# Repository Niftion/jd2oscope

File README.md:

## Project Status

- `3dmodels/`: Iteration 1 complete; iteration 2 WIP
  - Considering different potentiometer & button models (pot.s too small for knobs)
  - Looking into overhead enclosure for button/knob interface (i.e., transitioning from partially exposed to fully enclosed)
- `firmware/`: Iteration 1 WIP
  - Currently troubleshooting issues with SPI comm.; assumed resolution w/ the inclusion of tri-state buffer
  - Potentiometers laggy; assumed resolution w/ swap for rotary encoders
- `hardware/`: Iteration 1 complete; iteration 2 WIP
  - Adjustments needed to account for pullups/pulldowns & tri-state buffer
  - Considering swapping potentiometers for rotary encoders & using different buttons
  - Potentially re-evaluate netclasses/copper trace thicknesses
  - Flip around opAmp (for some reason was inverted in schematics)
  - Ensure all passives' values *actually exist* (if not, modify circuit to use ones that do)
  - Swap 5V LDO to buck converter (& generally re-evaluate power distribution method (currently not adequate for long-term usage))

## Project Leads

- `3dmodels/`: [@kaylauyema](https://github.com/kaylauyema)
  - *See [Onshape](https://cad.onshape.com/documents/8ccdb21e8d1079c729b3d0f6/w/fb9eb84c8df37a115b39a8e3/e/654db45d68c6c467c0a4227c?renderMode=0&uiState=67cde4469e5450083d885918) for all CAD files*
- `firmware/`: [@StPelican42](https://github.com/StPelican42)
- `hardware/`: [@Niftion](https://github.com/Niftion)

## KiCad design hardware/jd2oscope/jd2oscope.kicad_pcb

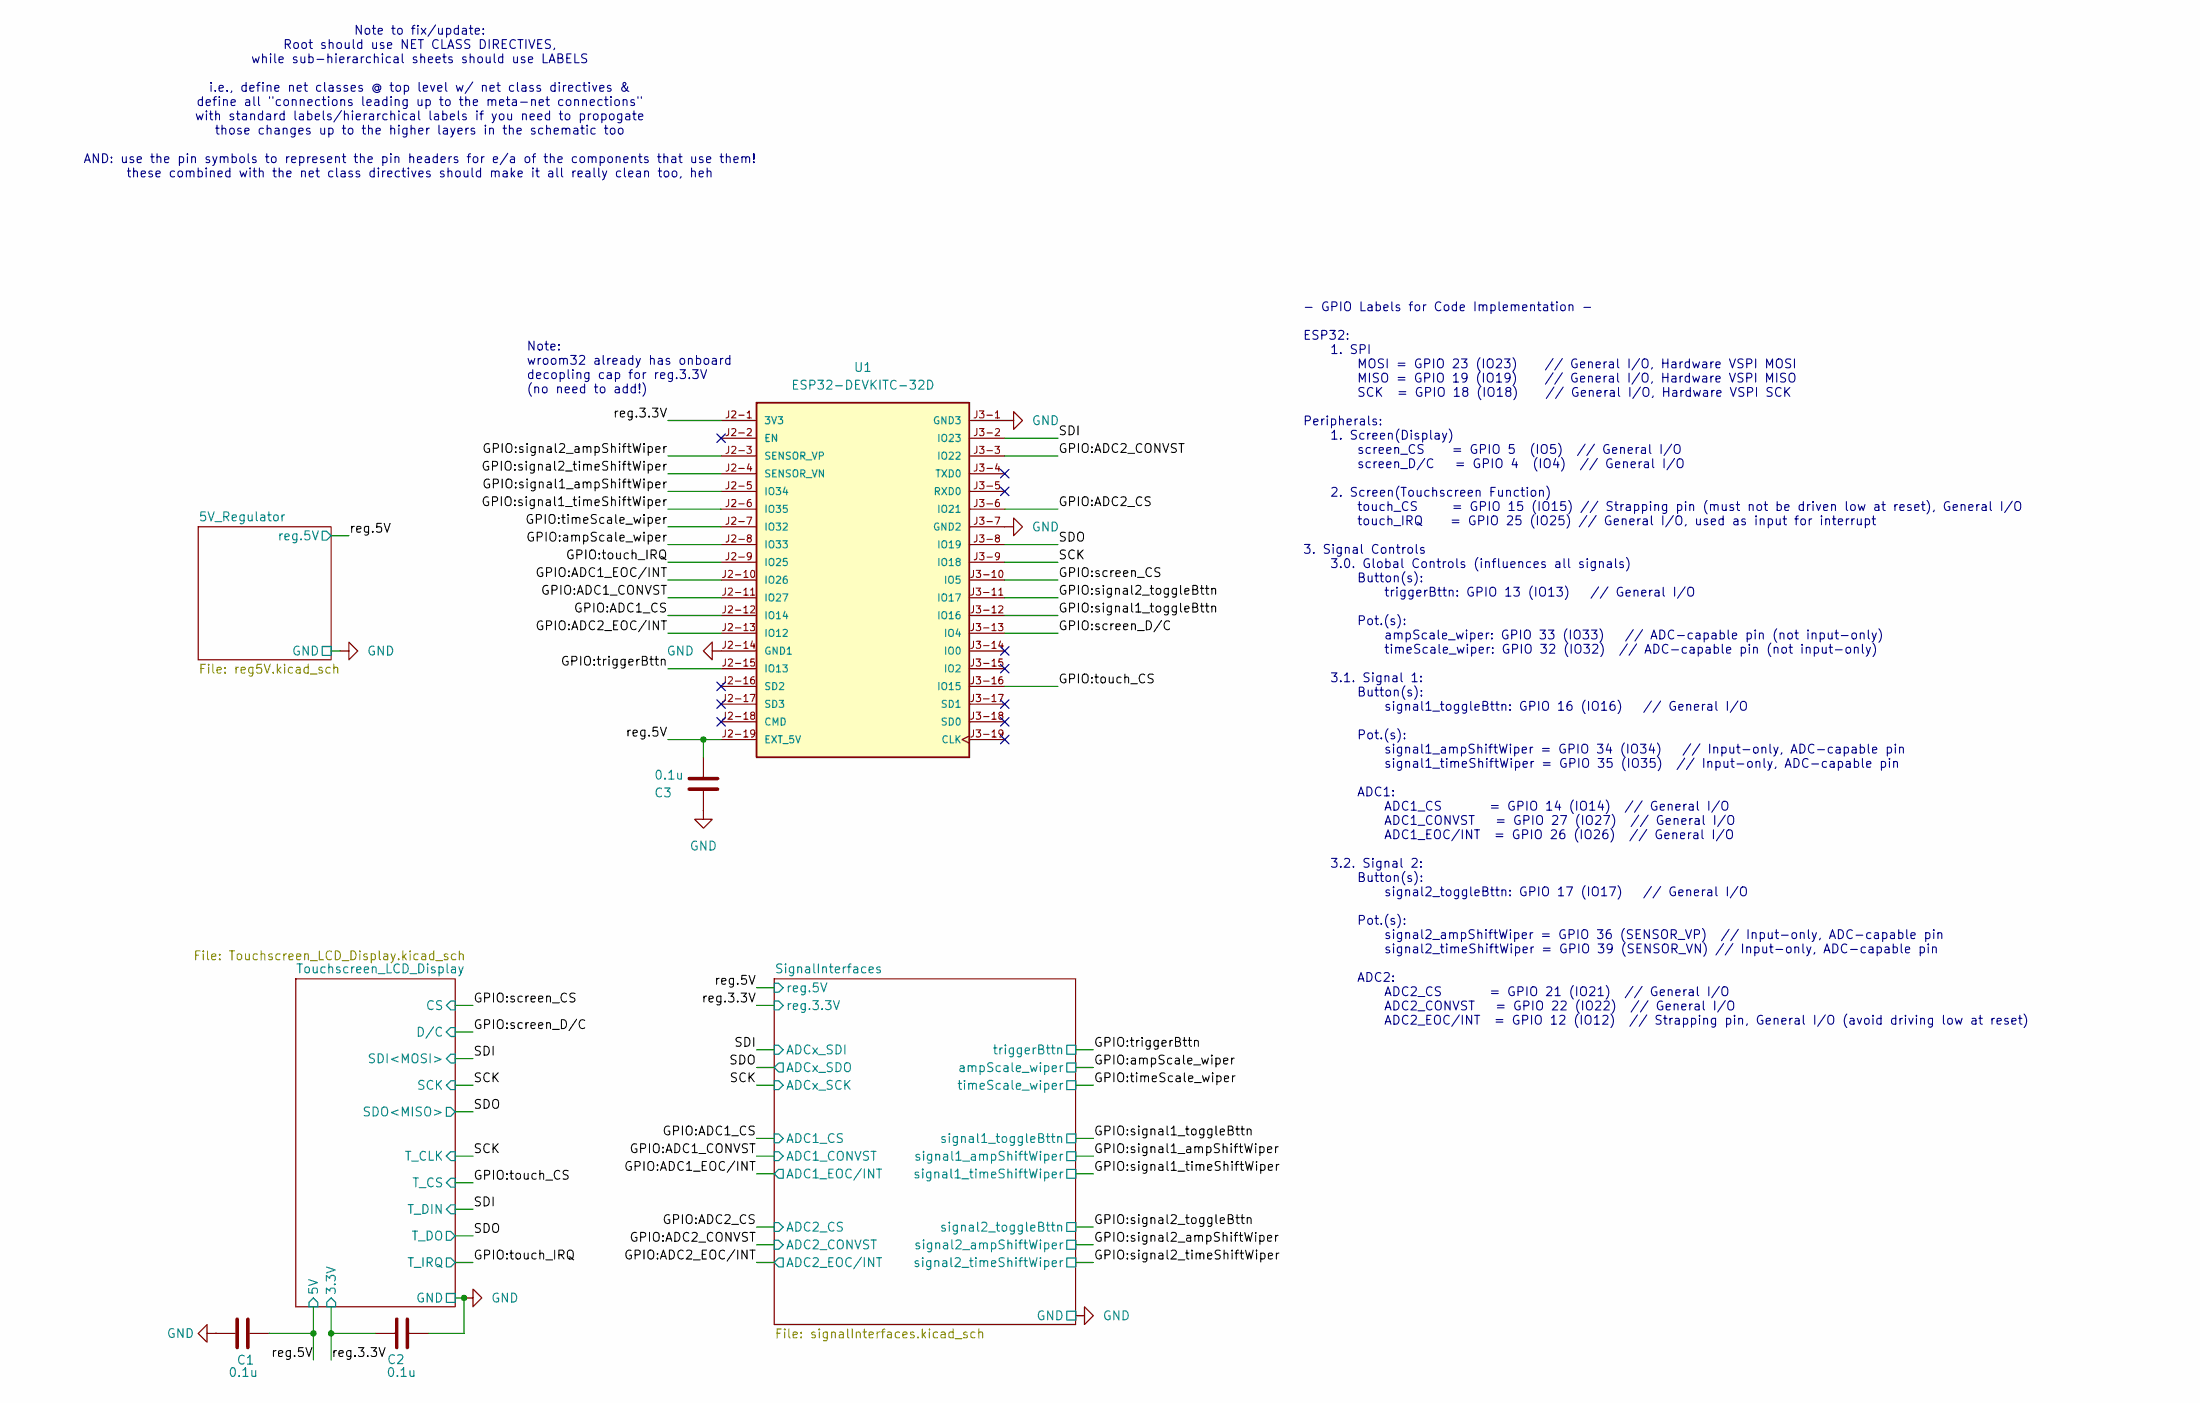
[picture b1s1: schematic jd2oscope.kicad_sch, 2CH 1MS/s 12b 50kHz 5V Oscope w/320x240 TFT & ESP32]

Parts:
C1, C2, C3: 0.1u; C_0603_1608Metric_Pad1.08x0.95mm_HandSolder
U1: ESP32-DEVKITC-32D; MODULE_ESP32-DEVKITC-32D; PARTREV V4; DigiKey_Part_Number 4166-ESP32-DEVKITC-32D-ND

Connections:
/GPIO:ADC1_CONVST: U1.J2-11 (IO27); also elsewhere on the board
/GPIO:ADC1_CS: U1.J2-12 (IO14); also elsewhere on the board
/GPIO:ADC1_EOC/INT: U1.J2-10 (IO26); also elsewhere on the board
/GPIO:ADC2_CONVST: U1.J3-3 (IO22); also elsewhere on the board
/GPIO:ADC2_CS: U1.J3-6 (IO21); also elsewhere on the board
/GPIO:ADC2_EOC/INT: U1.J2-13 (IO12); also elsewhere on the board
/GPIO:ampScale_wiper: U1.J2-8 (IO33); also elsewhere on the board
/GPIO:screen_CS: U1.J3-10 (IO5); also elsewhere on the board
/GPIO:screen_D/C: U1.J3-13 (IO4); also elsewhere on the board
/GPIO:signal1_ampShiftWiper: U1.J2-5 (IO34); also elsewhere on the board
/GPIO:signal1_timeShiftWiper: U1.J2-6 (IO35); also elsewhere on the board
/GPIO:signal1_toggleBttn: U1.J3-12 (IO16); also elsewhere on the board
/GPIO:signal2_ampShiftWiper: U1.J2-3 (SENSOR_VP); also elsewhere on the board
/GPIO:signal2_timeShiftWiper: U1.J2-4 (SENSOR_VN); also elsewhere on the board
/GPIO:signal2_toggleBttn: U1.J3-11 (IO17); also elsewhere on the board
/GPIO:timeScale_wiper: U1.J2-7 (IO32); also elsewhere on the board
/GPIO:touch_CS: U1.J3-16 (IO15); also elsewhere on the board
/GPIO:touch_IRQ: U1.J2-9 (IO25); also elsewhere on the board
/GPIO:triggerBttn: U1.J2-15 (IO13); also elsewhere on the board
/SCK: U1.J3-9 (IO18); also elsewhere on the board
/SDI: U1.J3-2 (IO23); also elsewhere on the board
/SDO: U1.J3-8 (IO19); also elsewhere on the board
/reg.3.3V: C2.2, U1.J2-1 (3V3); also elsewhere on the board
/reg.5V: C1.2, C3.2, U1.J2-19 (EXT_5V); also elsewhere on the board
GND: C1.1, C2.1, C3.1, U1.J2-14 (GND1), U1.J3-1 (GND3), U1.J3-7 (GND2); also elsewhere on the board

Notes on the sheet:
Note to fix/update: Root should use NET CLASS DIRECTIVES, while sub-hierarchical sheets should use LABELS i.e., define net classes @ top level w/ net class directives & define all "connections leading up to the meta-net connections" with standard labels/hierarchical labels if you need to propogate 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
- GPIO Labels for Code Implementation - ESP32: 1. SPI MOSI = GPIO 23 (IO23) // General I/O, Hardware VSPI MOSI MISO = GPIO 19 (IO19) // General I/O, Hardware VSPI MISO SCK = GPIO 18 (IO18) // General I/O, Hardware VSPI SCK Peripherals: 1. Screen(Display) screen_CS = GPIO 5 (IO5) // General I/O scre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
Note: wroom32 already has onboard decopling cap for reg.3.3V (no need to add!)

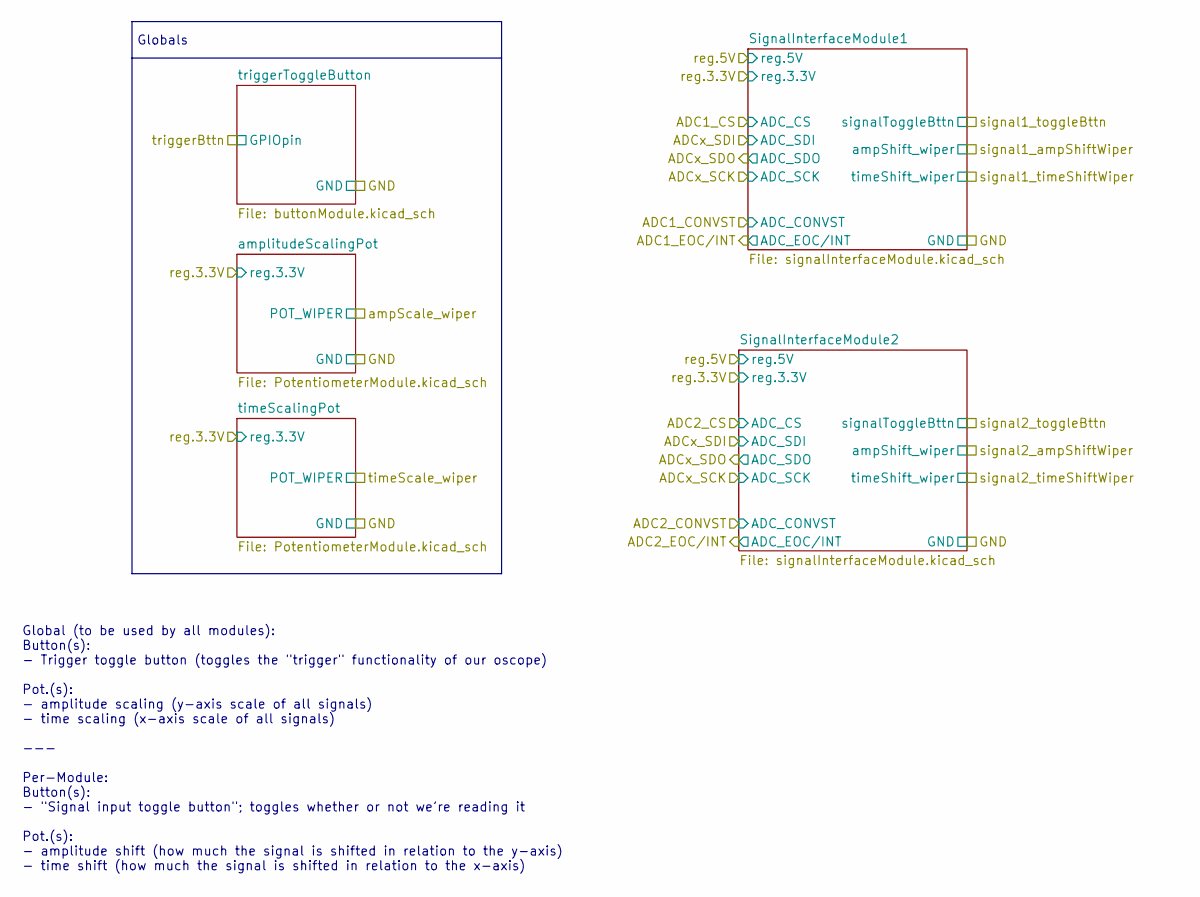
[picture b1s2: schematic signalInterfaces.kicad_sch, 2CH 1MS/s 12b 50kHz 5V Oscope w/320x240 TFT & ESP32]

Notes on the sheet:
Globals
Global (to be used by all modules): Button(s): - Trigger toggle button (toggles the "trigger" functionality of our oscope) Pot.(s): - amplitude scaling (y-axis scale of all signals) - time scaling (x-axis scale of all signals) --- Per-Module: Button(s): - "Signal input toggle button"; toggles wheth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

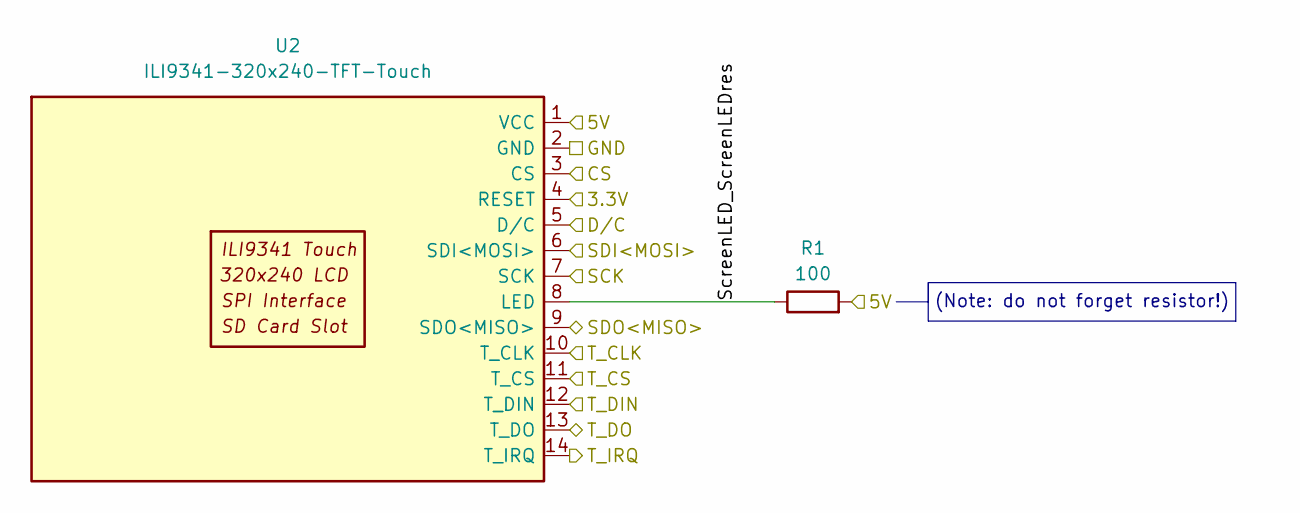
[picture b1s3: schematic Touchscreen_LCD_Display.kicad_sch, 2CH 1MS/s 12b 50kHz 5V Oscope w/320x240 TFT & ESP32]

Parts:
R1: 100; R_0603_1608Metric_Pad0.98x0.95mm_HandSolder
U2: ILI9341-320x240-TFT-Touch; PinHeader_1x14_P2.54mm_Vertical

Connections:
/GPIO:screen_CS: U2.3 (CS); also elsewhere on the board
/GPIO:screen_D/C: U2.5 (D/C); also elsewhere on the board
/GPIO:touch_CS: U2.11 (T_CS); also elsewhere on the board
/GPIO:touch_IRQ: U2.14 (T_IRQ); also elsewhere on the board
/SCK: U2.7 (SCK), U2.10 (T_CLK); also elsewhere on the board
/SDI: U2.6 (SDI<MOSI>), U2.12 (T_DIN); also elsewhere on the board
/SDO: U2.9 (SDO<MISO>), U2.13 (T_DO); also elsewhere on the board
/Touchscreen_LCD_Display/ScreenLED_ScreenLEDres: R1.1, U2.8 (LED)
/reg.3.3V: U2.4 (RESET); also elsewhere on the board
/reg.5V: R1.2, U2.1 (VCC); also elsewhere on the board
GND: U2.2 (GND); also elsewhere on the board

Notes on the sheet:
(Note: do not forget resistor!)

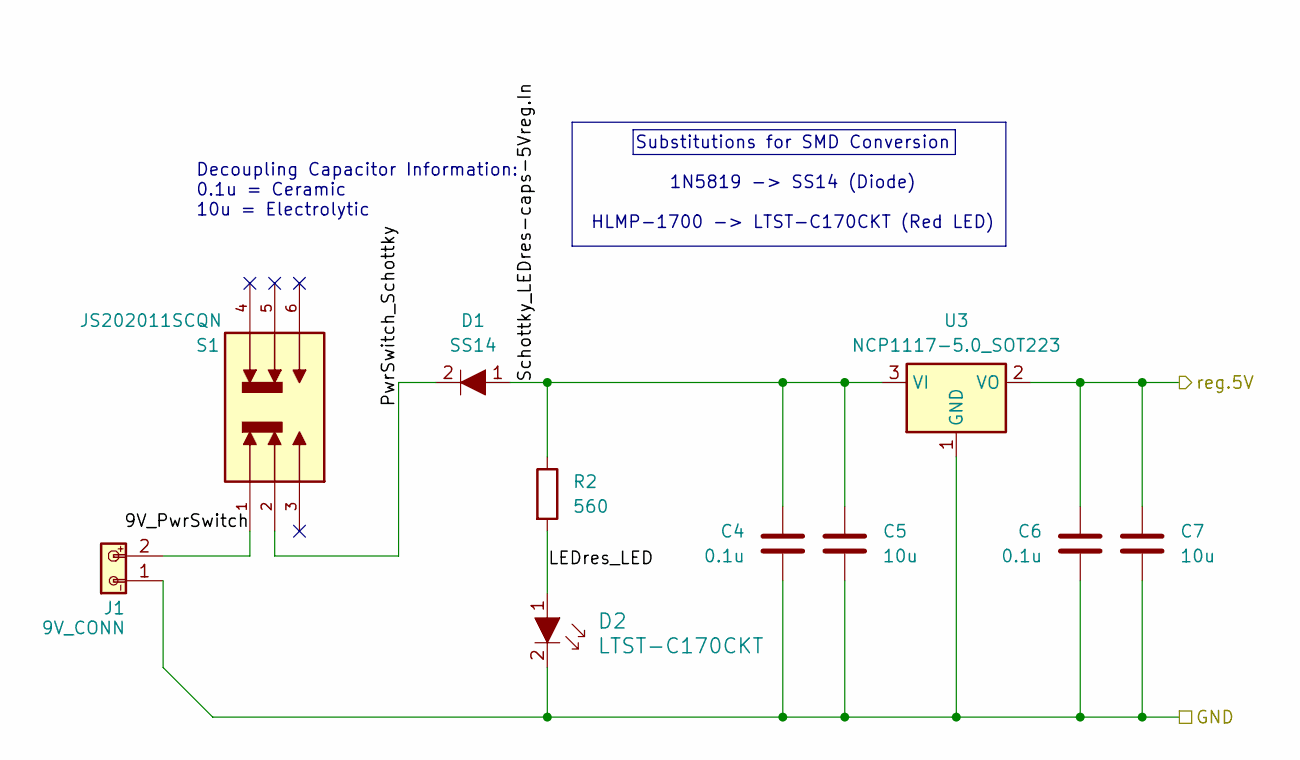
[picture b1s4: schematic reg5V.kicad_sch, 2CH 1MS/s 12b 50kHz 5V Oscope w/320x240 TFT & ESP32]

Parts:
C4, C6: 0.1u; C_0603_1608Metric_Pad1.08x0.95mm_HandSolder
C5, C7: 10u; C_0603_1608Metric_Pad1.08x0.95mm_HandSolder
D1: SS14; D_SOD-123; MPN SS14; Digi-Key_PN SS14CT-ND
D2: LTST-C170CKT; LED_0805_2012Metric; MPN LTST-C170KFKT; Digi-Key_PN 160-1184-1-ND
J1: 9V_CONN; TerminalBlock_RND_205-00001_1x02_P5.00mm_Horizontal
R2: 560; R_0603_1608Metric_Pad0.98x0.95mm_HandSolder
S1: JS202011SCQN; SW_JS202011SCQN; PARTREV 26 May 22
U3: NCP1117-5.0_SOT223; SOT-223-3_TabPin2

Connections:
/5V_Regulator/9V_PwrSwitch: J1.2, S1.1
/5V_Regulator/LEDres_LED: D2.1, R2.2
/5V_Regulator/PwrSwitch_Schottky: D1.2, S1.2
/5V_Regulator/Schottky_LEDres-caps-5Vreg.In: C4.2, C5.1, D1.1, R2.1, U3.3 (VI)
/reg.5V: C6.2, C7.1, U3.2 (VO); also elsewhere on the board
GND: C4.1, C5.2, C6.1, C7.2, D2.2, J1.1, U3.1 (GND); also elsewhere on the board

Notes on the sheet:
Substitutions for SMD Conversion 1N5819 -> SS14 (Diode) HLMP-1700 -> LTST-C170CKT (Red LED)
Decoupling Capacitor Information: 0.1u = Ceramic 10u = Electrolytic

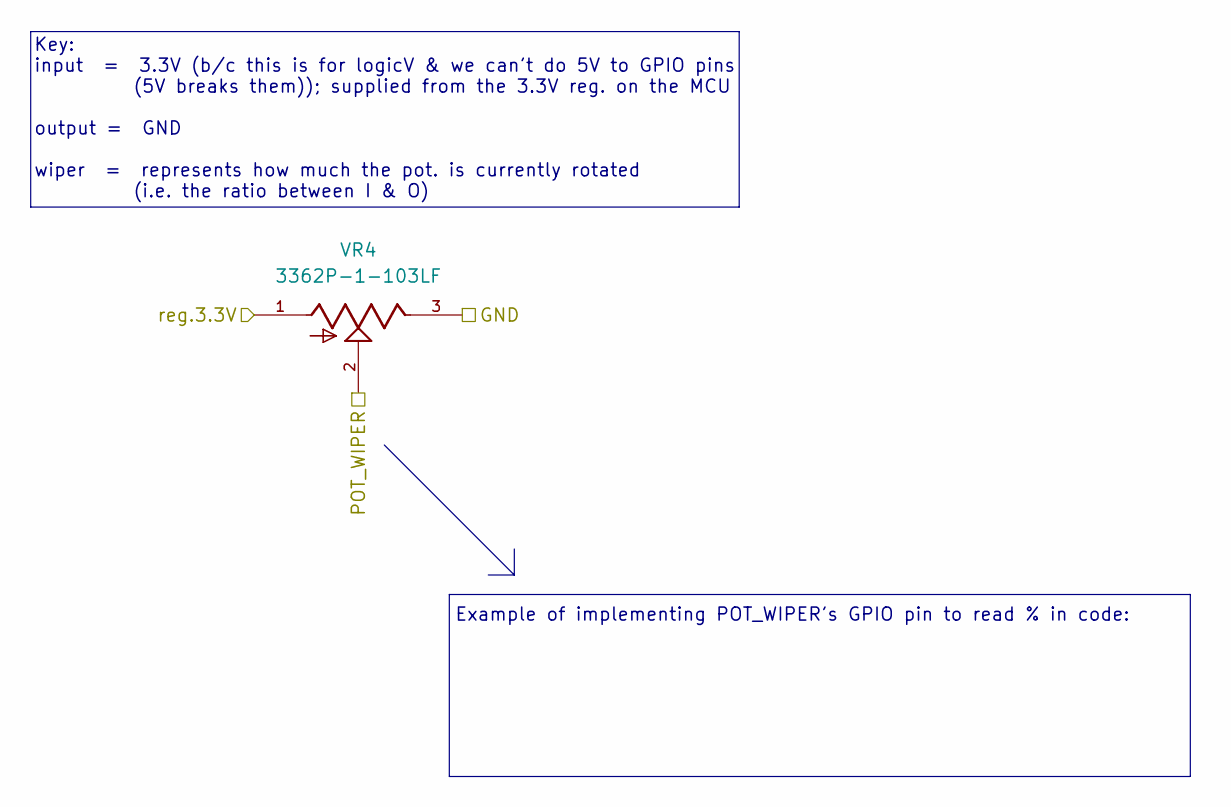
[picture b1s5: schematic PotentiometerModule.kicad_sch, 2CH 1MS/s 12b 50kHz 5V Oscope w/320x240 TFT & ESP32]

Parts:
VR4: 3362P-1-103LF; TRIM_3362P-1-103LF; PARTREV 08/26/10

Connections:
/GPIO:timeScale_wiper: VR4.2; also elsewhere on the board
/reg.3.3V: VR4.1; also elsewhere on the board
GND: VR4.3; also elsewhere on the board

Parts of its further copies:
VR1, VR2, VR3, VR5, VR6: 3362P-1-103LF; TRIM_3362P-1-103LF; PARTREV 08/26/10

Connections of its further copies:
/GPIO:ampScale_wiper: VR3.2; also elsewhere on the board
/GPIO:signal1_ampShiftWiper: VR1.2; also elsewhere on the board
/GPIO:signal1_timeShiftWiper: VR2.2; also elsewhere on the board
/GPIO:signal2_ampShiftWiper: VR5.2; also elsewhere on the board
/GPIO:signal2_timeShiftWiper: VR6.2; also elsewhere on the board
/reg.3.3V: VR1.1, VR2.1, VR3.1, VR5.1, VR6.1; also elsewhere on the board
GND: VR1.3, VR2.3, VR3.3, VR5.3, VR6.3; also elsewhere on the board

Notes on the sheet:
Key: input = 3.3V (b/c this is for logicV & we can't do 5V to GPIO pins (5V breaks them)); supplied from the 3.3V reg. on the MCU output = GND wiper = represents how much the pot. is currently rotated (i.e. the ratio between I & O)
Example of implementing POT_WIPER's GPIO pin to read % in code:

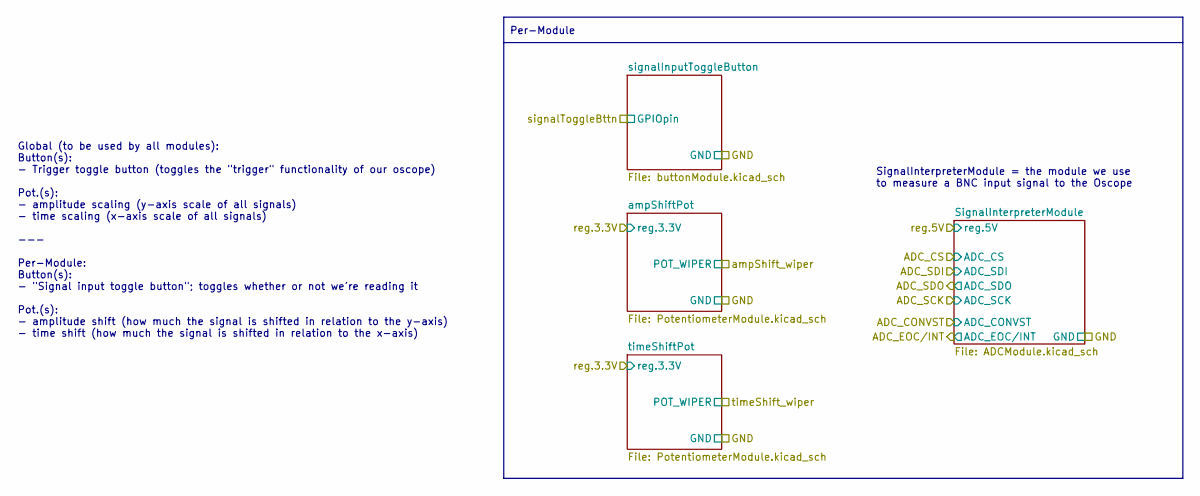
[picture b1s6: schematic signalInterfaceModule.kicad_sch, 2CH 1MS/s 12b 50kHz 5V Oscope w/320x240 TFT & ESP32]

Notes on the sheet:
Global (to be used by all modules): Button(s): - Trigger toggle button (toggles the "trigger" functionality of our oscope) Pot.(s): - amplitude scaling (y-axis scale of all signals) - time scaling (x-axis scale of all signals) --- Per-Module: Button(s): - "Signal input toggle button"; toggles wheth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
SignalInterpreterModule = the module we use to measure a BNC input signal to the Oscope
Per-Module

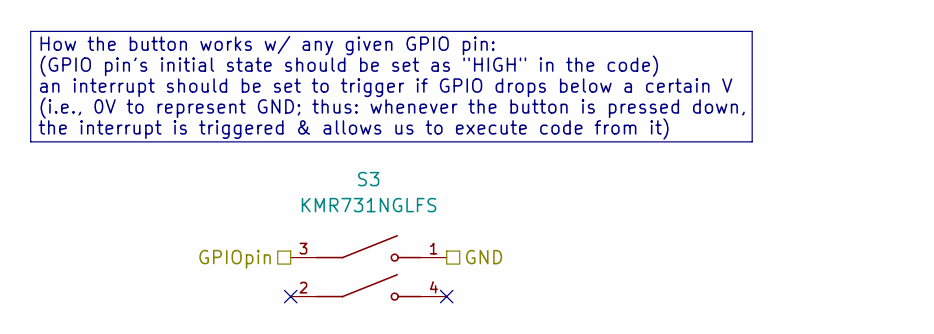
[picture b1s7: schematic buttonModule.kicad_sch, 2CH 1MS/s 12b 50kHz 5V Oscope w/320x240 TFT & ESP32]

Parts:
S3: KMR731NGLFS; SW_KMR731NGLFS; PARTREV N/A

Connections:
/GPIO:triggerBttn: S3.3; also elsewhere on the board
GND: S3.1; also elsewhere on the board

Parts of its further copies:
S2, S4: KMR731NGLFS; SW_KMR731NGLFS; PARTREV N/A

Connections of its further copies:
/GPIO:signal1_toggleBttn: S2.3; also elsewhere on the board
/GPIO:signal2_toggleBttn: S4.3; also elsewhere on the board
GND: S2.1, S4.1; also elsewhere on the board

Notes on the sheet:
How the button works w/ any given GPIO pin: (GPIO pin's initial state should be set as "HIGH" in the code) an interrupt should be set to trigger if GPIO drops below a certain V (i.e., 0V to represent GND; thus: whenever the button is pressed down, the interrupt is triggered & allows us to execute c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

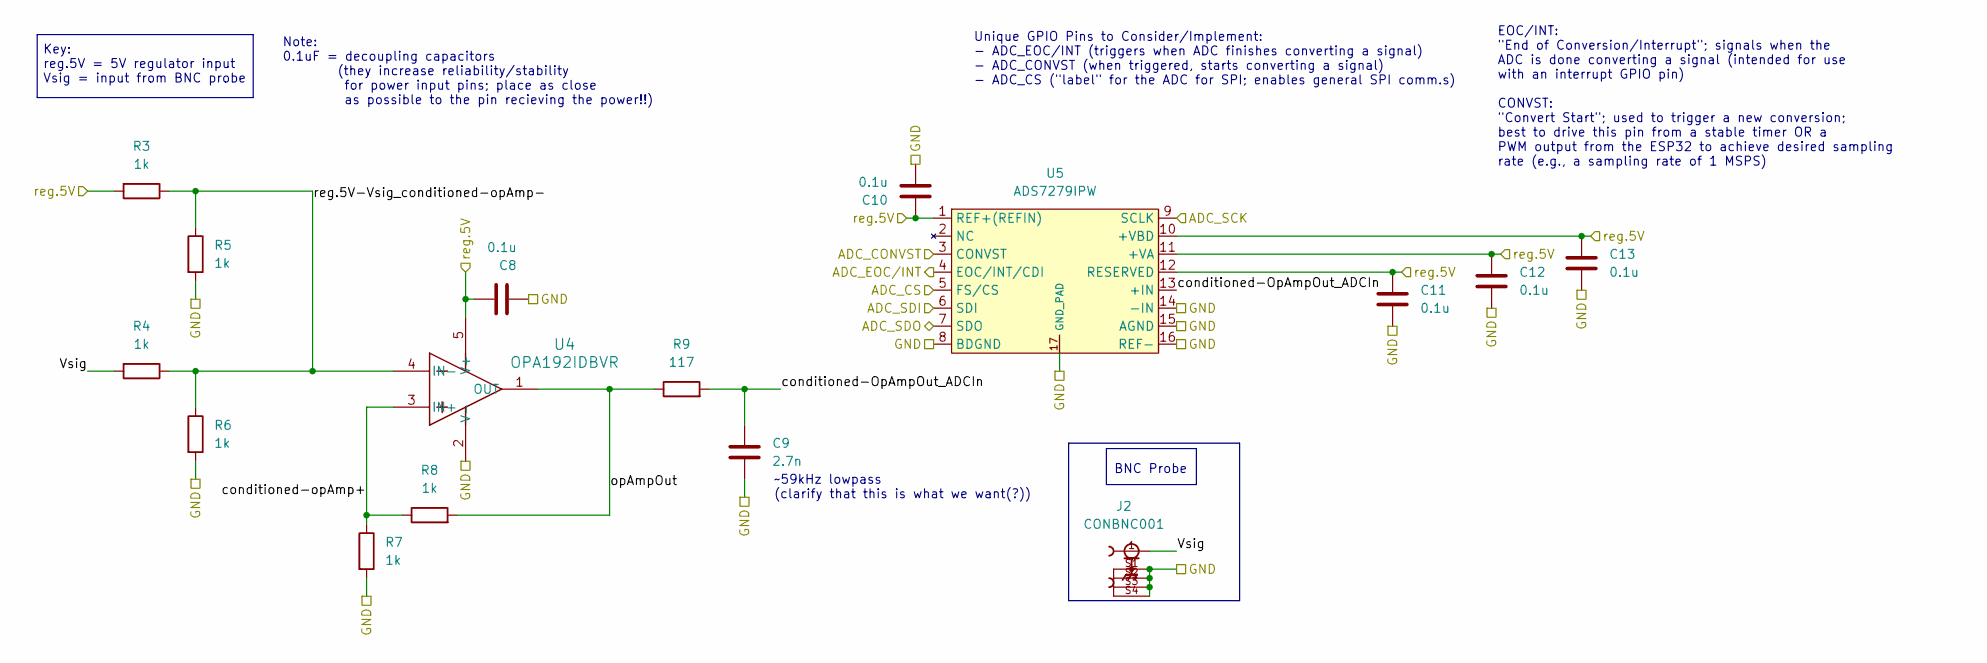
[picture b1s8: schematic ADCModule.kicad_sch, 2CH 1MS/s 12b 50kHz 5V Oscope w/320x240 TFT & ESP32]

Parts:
C8, C10, C11, C12, C13: 0.1u; C_0603_1608Metric_Pad1.08x0.95mm_HandSolder
C9: 2.7n; C_0603_1608Metric_Pad1.08x0.95mm_HandSolder
J2: CONBNC001; LINX_CONBNC001
R3, R4, R5, R6, R7, R8: 1k; R_0603_1608Metric_Pad0.98x0.95mm_HandSolder
R9: 117; R_0603_1608Metric_Pad0.98x0.95mm_HandSolder
U4: OPA192IDBVR; SOT95P280X145-5N
U5: ADS7279IPW; LFCSP-16-1EP_4x4mm_P0.65mm_EP2.6x2.6mm

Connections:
/GPIO:ADC1_CONVST: U5.3 (CONVST); also elsewhere on the board
/GPIO:ADC1_CS: U5.5 (FS/CS); also elsewhere on the board
/GPIO:ADC1_EOC/INT: U5.4 (EOC/INT/CDI); also elsewhere on the board
/SCK: U5.9 (SCLK); also elsewhere on the board
/SDI: U5.6 (SDI); also elsewhere on the board
/SDO: U5.7 (SDO); also elsewhere on the board
/SignalInterfaces/SignalInterfaceModule1/SignalInterpreterModule/Vsig: J2.1, R4.2
/SignalInterfaces/SignalInterfaceModule1/SignalInterpreterModule/conditioned-Op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: C9.1, R9.2, U5.13 (+IN)
/SignalInterfaces/SignalInterfaceModule1/SignalInterpreterModule/conditioned-op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: R7.1, R8.1, U4.3 (IN+)
/SignalInterfaces/SignalInterfaceModule1/SignalInterpreterModule/opAmpOut: R8.2, R9.1, U4.1 (OUT)
/SignalInterfaces/SignalInterfaceModule1/SignalInterpreterModule/reg.5V-Vsig_co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: R3.1, R4.1, R5.1, R6.1, U4.4 (IN-)
/reg.5V: C8.1, C10.1, C11.1, C12.1, C13.1, R3.2, U4.5 (V+), U5.1 (REF+(REFIN)), U5.10 (+VBD), U5.11 (+VA), U5.12 (RESERVED); also elsewhere on the board
GND: C8.2, C9.2, C10.2, C11.2, C12.2, C13.2, J2.S1, J2.S2, J2.S3, J2.S4, R5.2, R6.2, R7.2, U4.2 (V-), U5.8 (BDGND), U5.14 (-IN), U5.15 (AGND), U5.16 (REF-), U5.17 (GND_PAD); also elsewhere on the board

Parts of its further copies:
C14, C16, C17, C18, C19: 0.1u; C_0603_1608Metric_Pad1.08x0.95mm_HandSolder
C15: 2.7n; C_0603_1608Metric_Pad1.08x0.95mm_HandSolder
J3: CONBNC001; LINX_CONBNC001
R10, R11, R12, R13, R14, R15: 1k; R_0603_1608Metric_Pad0.98x0.95mm_HandSolder
R16: 117; R_0603_1608Metric_Pad0.98x0.95mm_HandSolder
U6: OPA192IDBVR; SOT95P280X145-5N
U7: ADS7279IPW; LFCSP-16-1EP_4x4mm_P0.65mm_EP2.6x2.6mm

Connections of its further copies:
/GPIO:ADC2_CONVST: U7.3 (CONVST); also elsewhere on the board
/GPIO:ADC2_CS: U7.5 (FS/CS); also elsewhere on the board
/GPIO:ADC2_EOC/INT: U7.4 (EOC/INT/CDI); also elsewhere on the board
/SCK: U7.9 (SCLK); also elsewhere on the board
/SDI: U7.6 (SDI); also elsewhere on the board
/SDO: U7.7 (SDO); also elsewhere on the board
/SignalInterfaces/SignalInterfaceModule2/SignalInterpreterModule/Vsig: J3.1, R11.2
/SignalInterfaces/SignalInterfaceModule2/SignalInterpreterModule/conditioned-Op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: C15.1, R16.2, U7.13 (+IN)
/SignalInterfaces/SignalInterfaceModule2/SignalInterpreterModule/conditioned-op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: R14.1, R15.1, U6.3 (IN+)
/SignalInterfaces/SignalInterfaceModule2/SignalInterpreterModule/opAmpOut: R15.2, R16.1, U6.1 (OUT)
/SignalInterfaces/SignalInterfaceModule2/SignalInterpreterModule/reg.5V-Vsig_co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: R10.1, R11.1, R12.1, R13.1, U6.4 (IN-)
/reg.5V: C14.1, C16.1, C17.1, C18.1, C19.1, R10.2, U6.5 (V+), U7.1 (REF+(REFIN)), U7.10 (+VBD), U7.11 (+VA), U7.12 (RESERVED); also elsewhere on the board
GND: C14.2, C15.2, C16.2, C17.2, C18.2, C19.2, J3.S1, J3.S2, J3.S3, J3.S4, R12.2, R13.2, R14.2, U6.2 (V-), U7.8 (BDGND), U7.14 (-IN), U7.15 (AGND), U7.16 (REF-), U7.17 (GND_PAD); also elsewhere on the board

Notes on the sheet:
Key: reg.5V = 5V regulator input Vsig = input from BNC probe
~59kHz lowpass (clarify that this is what we want(?))
EOC/INT: "End of Conversion/Interrupt"; signals when the ADC is done converting a signal (intended for use with an interrupt GPIO pin) CONVST: "Convert Start"; used to trigger a new conversion; best to drive this pin from a stable timer OR a PWM output from the ESP32 to achieve desired sampling rat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
Note: 0.1uF = decoupling capacitors (they increase reliability/stability for power input pins; place as close as possible to the pin recieving the power!!)
BNC Probe
Unique GPIO Pins to Consider/Implement: - ADC_EOC/INT (triggers when ADC finishes converting a signal) - ADC_CONVST (when triggered, starts converting a signal) - ADC_CS ("label" for the ADC for SPI; enables general SPI comm.s)

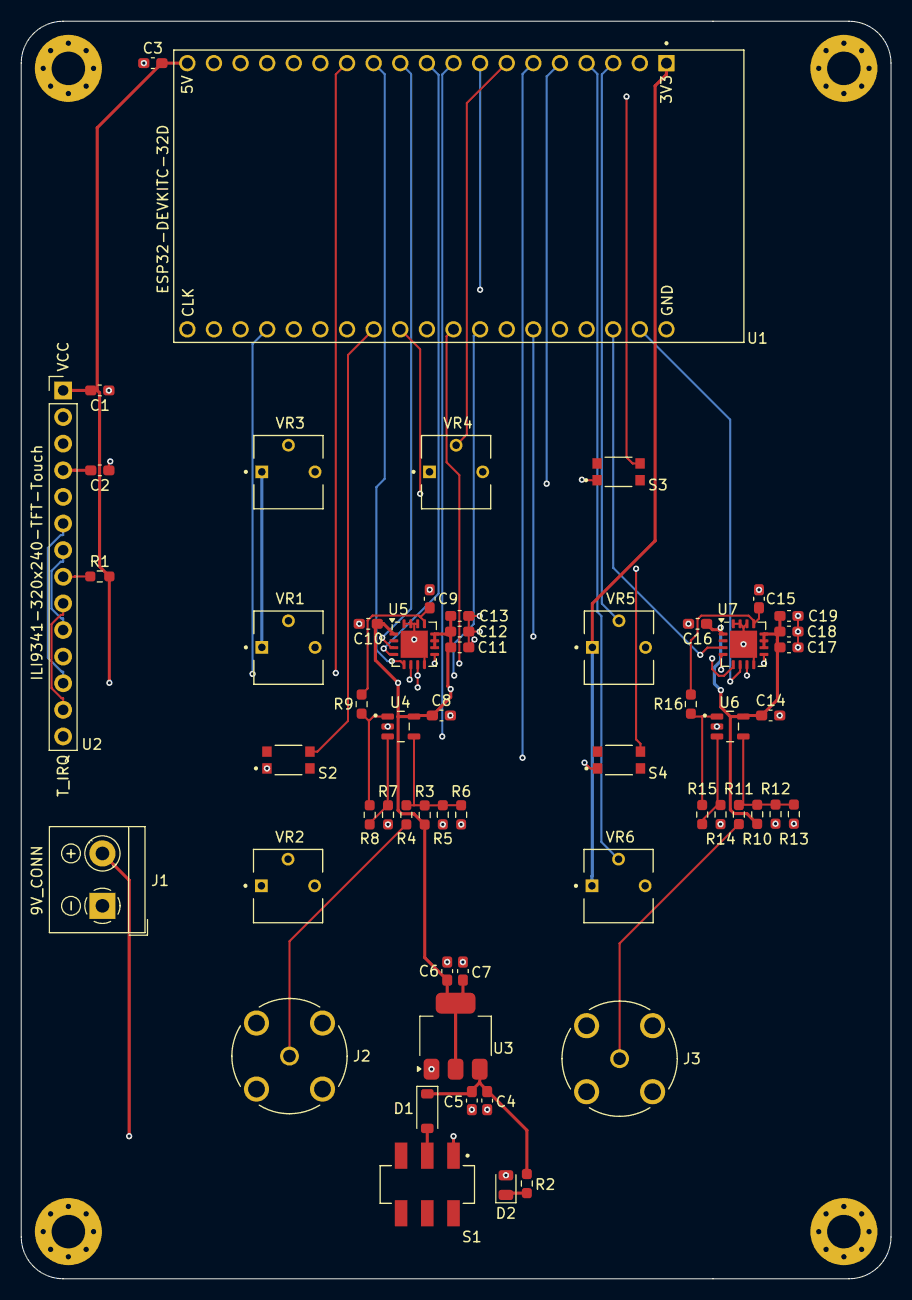
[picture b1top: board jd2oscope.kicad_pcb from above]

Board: 4 copper layers, 83.0 x 120.0 mm, 61 parts (0 on the bottom side), 40 nets.

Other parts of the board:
REF1, REF2, REF3, REF4: MountingHole_3.2mm_M3_Pad_Via

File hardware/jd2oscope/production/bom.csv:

Designator,Footprint,Quantity,Value,LCSC Part #
"C1, C10, C11, C12, C13, C14, C16, C17, C18, C19, C2, C3, C4, C6, C8",0603,15,0.1u,
"C15, C9",0603,2,2.7n,
"C5, C7",0603,2,10u,
D1,D_SOD-123,1,SS14,SS14
D2,0805,1,LTST-C170CKT,LTST-C170KFKT
J1,TerminalBlock_RND_205-00001_1x02_P5.00mm_Horizontal,1,9V_CONN,
"J2, J3",LINX_CONBNC001,2,CONBNC001,
R1,0603,1,100,
"R10, R11, R12, R13, R14, R15, R3, R4, R5, R6, R7, R8",0603,12,1k,
"R16, R9",0603,2,117,
R2,0603,1,560,
S1,SW_JS202011SCQN,1,JS202011SCQN,
"S2, S3, S4",SW_KMR731NGLFS,3,KMR731NGLFS,
U1,MODULE_ESP32-DEVKITC-32D,1,ESP32-DEVKITC-32D,
U2,PinHeader_1x14_P2.54mm_Vertical,1,ILI9341-320x240-TFT-Touch,
U3,SOT-223-3_TabPin2,1,NCP1117-5.0_SOT223,
"U4, U6",SOT95P280X145-5N,2,OPA192IDBVR,
"U5, U7",LFCSP-16-1EP_4x4mm_P0.65mm_EP2.6x2.6mm,2,ADS7279IPW,
"VR1, VR2, VR3, VR4, VR5, VR6",TRIM_3362P-1-103LF,6,3362P-1-103LF,

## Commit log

2025-01-16 first
2025-01-16 feat: folder for CAD files
2025-01-23 block diagrams
2025-01-28 feat: kicad board dev
    parts added, general framework established
2025-01-28 platformIO setup
2025-01-28 ADC KiCAD
2025-01-29 fix: relative file paths
    added relative file paths for symbols & footprints such that everyone can access them on any machine they clone to
2025-01-29 feat: opAmpCircuit cleanup
2025-01-29 feat: more reorganizing of adc
2025-01-29 feat: small tweaks to adc schematic structure
2025-01-29 fix: adc schematic structure v3
    small tweak; likely the last thing for now
2025-01-30 fix: pushing so people can edit!! (I think)
2025-01-30 feat: uploaded drivers
2025-02-14 added ADC 2
2025-02-15 feat: signals processing module
    added
2025-02-15 fix: JD342 ADC now opens properly
    there was an issue with having two kicad_sch files in the directory; replaced the old one w/ the new one & was able to fix it & thereafter view successfully
2025-02-19 feat: screen implemented
    alongside screen implementation, re-structured layout for schematics, and cleaned up SPI comm. conn.s; also implemented ADC module successfully (sans SPI section for it; that comes next)
2025-02-19 feat: added .gitignore
2025-02-19 fix: gitignore to ignore kiCad backups
2025-02-19 feat: lot of progress
    added decoupling caps, implemented a lot more of the comm. protocol stuffs, updated BNC connector to updated version, added more notes for GPIO pin I/O for future code implementation, lot of other st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
2025-02-19 feat: more stuff added
    yep
2025-02-19 feat: finished schematics
    I think! Subject to change tho! for now though at least, I think they look clean asf hah~
2025-02-19 fix: added NCs
    forgot to add NCs to Wroom32 dev board; they are now added!
2025-02-20 fix: schematic page numbers
    they were out of order & weird, so I fixed them; should be good now! (there are 17 in total, let's go)
2025-02-20 fix: added sym & ftprnt for esp32
    was using my local versions; added the actual sym and footprint files to the repo & changed library references to them so that everyone can access them too
2025-02-20 feat: added 3dModel STEP for esp32
    got it from snapEDA; still need to associate it with the footprint, however this is a good start
2025-02-20 fix: ERC funtimes
    fixed a bunch of dependencies with ERC checks for the schematic; shouuuuld be easier/actually possible to open on other devices now?? (added a buncha schematics & footprints to the local files & what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
2025-02-20 fix: footprint/symbol fixes for ILI9341_Touch
    blegh
2025-02-20 feat: ERC is now happy!
    We now pass all ERC checks in terms of errors; it is now fully satisfied!! (and, any warnings are just due to the fact that we made local edits to global symbol values, so we're ballin' all the way f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
2025-02-20 feat/fix: no more errors for PCB import too!
    Now both the ERC, and the schematic import (and my OCD) are completely satisfied, and we can dev the actual PCB; let's go!! :D
2025-02-20 feat:net lists & net classes implemented
    labeled e/a net w/ net labels to clarify nodes, & created net classes w/ desired dimensions for traces; next up is assigning net classes to e/a net & using it to create the pcb!
2025-02-20 feat: labeled net classes on root
    lolz
2025-02-20 3d models
    3d models uploaded
2025-02-20 feat: Block 1 Testing
    Very early draft.
2025-02-20 feat: pcb progress
2025-02-21 feat: pcb complete
    ha gottem
2025-02-21 feat: pcb 3d model
    exported pcb 3d model (hopefully looks good?)
2025-02-21 feat: noTracks PCB STEP too
    because the one with tracks was really big and I wanted to see if this smaller version would let me view it on github lol
2025-02-21 feat: BOM (Bill of Materials added)
    yipeee
2025-02-21 fix: moved BOM to top level
    because it looks better there & not lost in the sea of kicad files it was otherwise in lol
2025-02-22 fix: M4 -> M3 & re-exported 3d models
    3d models now represent M3 board instead of M4 board (the mounting holes); I also added a cooler version with copper and vias, because well, it looks cooler (and also for "improved structural integri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
2025-02-22 fix: arbitrary grammar thing in comment
    noticed a ) was missing from one of the text blocks in the schematic, so I added one :P
2025-02-22 feat: more 3d models stuffs
    woah
2025-02-22 feat: silkscreen updates
    note that DRC now produces warnings for some of the silkscreens on the back of the PCB. I am under the impression that they don't matter that much, & hoping it "just works"; if anything, minor bleed 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
2025-02-23 fix: added change note
    note to change root labels to net class directives; will implement in the future, just wanted to put smth there so I remember to
2025-02-23 fix: added another update note
    this time for how to properly represent the pin headers in the schematic; will update accordingly at a later date, just wanted to note something down in the meantime so I don't forget
2025-02-25 new 3d prints
2025-02-25 replaced bottom and top print
2025-02-27 feat: font tweaks
    nothing that big tbh
2025-02-27 feat: filled in title block
    added relevant information to schematic title block blurb in the lower right
2025-02-27 fix: propagated group name to all sheets
    before it was just on the root; forgot to click the "apply to all sheets" textbox thingie
2025-03-01 feat: firmware testing scripts for esp32
    for block 2 checkoff; added in firmware section (not relevant to main oscilloscope's functionality)
2025-03-01 fix: schematic labels
2025-03-01 fix: undid the thing that I thought was a fix
    it is actually 12b still lol
2025-03-02 chore: undo lock files
    oops these weren't supposed to be pushed; should add these to the gitignore tbh
2025-03-02 Start of Module 3- display settings
    Trying to get the display to work. All else has been commented out.
2025-03-02 fix: ILI9341 Library conflict
    To fix: switched to Bodmer's library instead; compiles on my end now. There was also a bunch of weird issues w/ the cache; those are good now too. Also added User_Setup.h; this is a req. of the Bodme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
2025-03-02 chore: remove lock file
2025-03-04 First working draft of display
    First working draft of using Bodmer TFT display library
2025-03-04 Early draft graph setup
    Early demo model of the graph UI, taken from the Bodmer eTFT library and TFT widget library
2025-03-04 Latest version of Graph display testing
    Latest version of Graph display testing
2025-03-06 Zoom with arduino timing
    Display with zoom, amplitude, and arduino timing. Only meant for prototyping so far.
2025-03-06 Prototype Display with pause
    Used interrupts on GPIO26 for pausing the screen. Paused screen looks hazy due to constantly updating the screen.
2025-03-06 Display with pause v2
    This version gets rid of the fuzzy pause screen but doesn't register for every button press (maybe because I'm using shaky jumper wires, maybe its the code)
2025-03-06 Prototype Display with TRIGGER
    Trigger also implemented using interrupts. Trigger function collects the first 200 data points and sifts through them until it finds 5 consecutive rising or falling points, then displays the rest of 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
2025-03-06 Prototype code with trigger, zoom, Amplitude, and pause
    Edited to have less garbage pseudocode. Easier to read now.
2025-03-07 chore: removed DS_Store files
2025-03-07 chore: updated 3d files
    added new enclosure files, updated naming schemes, added potentiometer knobs for voltage and time
2025-03-07 Updated neatness + trigger
    New trigger function allows for faster data collection(IDK why i thought collecting double the samples for every frame was a good idea
2025-03-07 feat: better BOM file
    looks pr cool ngl
2025-03-08 feat: note on important fix for screen function
2025-03-08 feat: code updates
    general fixes
2025-03-08 feat: pin assignments initialized
    also aligned with naming scheme in kicad
2025-03-08 Pin update with latest SPI attempt
    We're getting close to the goal...
2025-03-08 feat: testing firmware
2025-03-09 feat: testing files
    note: they do not really work atm
2025-03-09 fix: duplicate declarations
    condensed duplicate declarations; moved them all to Oscilloscope.h & fixed a few var types too
2025-03-09 Latest version: bit banging spi attempt
    This version tries to use the bit banging approach as the arduino SPI library might not work with our setup.
2025-03-10 feat: updated capacitor values
    and other fixes too
2025-03-10 chore: re-organizing files
2025-03-13 Last or 2nd to last push
    Theres still a huge delay whhen receiving analog input. Hopefully adding the buffers will straighten things out.
2025-03-16 Update README.md
    added links to e/a contributors' GitHub profile
2025-03-16 feat: 100th Commit (!!)
    No real changes, I just wanted to make the 100th commit ;)
